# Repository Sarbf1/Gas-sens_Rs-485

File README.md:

# Gas-sens_Rs-485
a Compact, cheap gas sensor with RS-485 connectivity

## Concept:
24V supplied, Gas detector with half-duplex RS-485 interface. For industrial or home use and application ready product, containing a current or voltage output for reference measurment.
a sinlge LED used for showing cominucation or Error state. The small footprint makes it ready for most plastic enclosures.
the PCB can be hand-solderd with a bit of skill. 
Use cases can be in Garage systems (linked with the vents and gas alarm system), hobbyist workshop or any other room such as Office spaces and schools.

## Components

A STM32G031K8 is the logical unit. Is is cheap and readily available.
The very most components use standart fooprints. Thus, they are easily exchangeble in case of a shortage.
All parts are SMD, except for the Sensors, DCDC converter and Connectors.
All PCB components can be sourced by Mouser, except for the Gas Sensor.
For developement purposes (TAG v0.1) a gas sensor type MQ-X were used (MQ-7 and MQ-135)
TAG v0.2 makes use of the nemoto sensor, that uses low current and is more gas specific. 
The I2C conection gives a possibility, to further extend with more sensors, such as the Sensirion SHT4X.

## Programming
Hardware is developed in KiCad 7.0.

everything is programmed on STM Cube IDE. The Sensor and trim potentiometers are read-in using DMA.
The max and minimum values of the potentiometers can be set by the Modbus. the specific address are found in the excel-table "Modbus-memorymap" in the software folder.

## Simulation
Low pass filter for the PWM (from uC to OpAmp to voltag eand current output) has been simulated using LTSpice.

## next steps
- [X] PWM filter simulations
- [x] build and test prototype
- [x] Prgram IC for analog measurment and analog output
- [x] Find better sensor supplier and include it on second version PCB -> nemoto sensors
- [x] implement Modbus via RS-485
- [ ] create Bill of material
- [x] Make second physical prototype

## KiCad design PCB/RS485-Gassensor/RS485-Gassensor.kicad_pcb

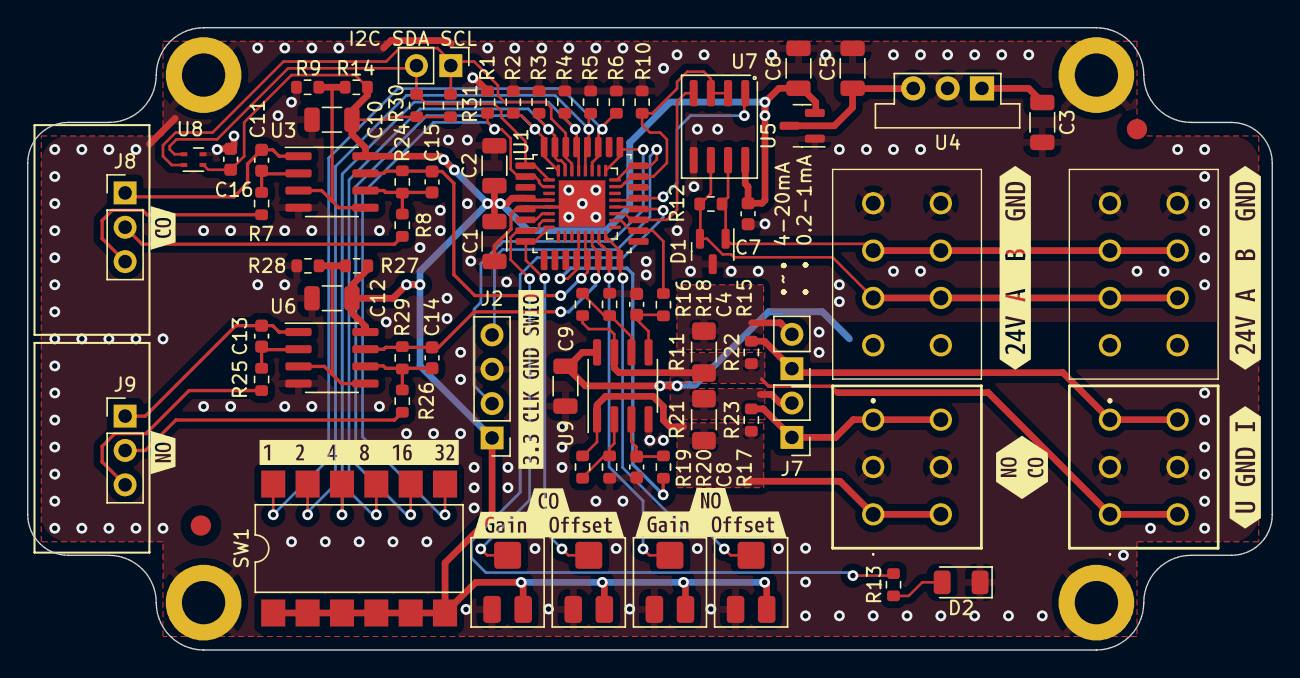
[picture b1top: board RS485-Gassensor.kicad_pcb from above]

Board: 2 copper layers, 92.0 x 46.0 mm, 91 parts (0 on the bottom side), 52 nets.

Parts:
C1: CAP4.7uF; C_1206_3216Metric
C2: CAP100nF; C_1206_3216Metric
C3: CAP10uF; C_1206_3216Metric
C4, C8: 470nF; C_0603_1608Metric
C5: CAP22uF; C_1206_3216Metric
C6, C9, C10, C12: CAP1uF; C_1206_3216Metric
C7, C16: CAP100nF; C_0603_1608Metric
C11, C13, C14, C15: CAP1uF; C_0603_1608Metric
D1: SM712_SOT23; SOT-23
D2: IR26-21C_L110_TR8; LED_1206_3216Metric
FID1, FID2: Fiducial; Fiducial_1.5mm_Mask3mm
H1, H2, H3, H4: MountingHole_Pad; MountingHole_3.2mm_M3_DIN965_Pad
J1, J3: Screw_Terminal_01x08; 1862068
J2: Screw_Terminal_01x04; PinHeader_1x04_P2.54mm_Vertical
J4, J5: Screw_Terminal_01x06; 1071000
J6, J7: Conn_01x02_Pin; PinHeader_1x02_P2.54mm_Vertical
J8, J9: Conn_01x03; PinHeader_1x03_P2.54mm_Vertical
J10: Conn_01x02; PinHeader_1x02_P2.54mm_Vertical
R1, R2, R3, R4, R5, R6, R7, R10, R24, R25, R29, R30, R31: R10K; R_0603_1608Metric
R8, R26: 10; R_0603_1608Metric
R9, R15, R17, R27, R28: 1k; R_0603_1608Metric
R11, R21: R470; R_1206_3216Metric_Pad1.30x1.75mm_HandSolder
R12: R220; R_0603_1608Metric
R13: R100; R_0603_1608Metric
R14, R16, R19: 2.2k; R_0603_1608Metric
R18, R20: R1K; R_0603_1608Metric
R22, R23: 10KR; R_0603_1608Metric
RV1, RV2, RV3, RV4: R_Poti_1K; Potentiometer_Bourns_3214J_Horizontal
SW1: SW_DIP_x06; SMDIP-12_W9.53mm
U1: STM32G031K8Tx; LQFP-32_7x7mm_P0.8mm
U2: STM32G031K8Ux; QFN-32-1EP_5x5mm_P0.5mm_EP3.45x3.45mm
U3, U6: MCP6002-xMS; SOIC-8_3.9x4.9mm_P1.27mm
U4: OKI-78SR-5_1.5-W36-C; Converter_DCDC_Murata_OKI-78SR_Vertical
U5: AP2127N-3.3; SOT-23
U7: LT1785xS8; SOIC-8_3.9x4.9mm_P1.27mm
U8: SHT4x; Sensirion_DFN-4_1.5x1.5mm_P0.8mm_SHT4x_NoCentralPad
U9: AD8676; SOIC-8_3.9x4.9mm_P1.27mm
kibuzzard-64E925B6: G***; kibuzzard-64E925B6
kibuzzard-64E958EB: G***; kibuzzard-64E958EB
kibuzzard-64E958FD: G***; kibuzzard-64E958FD
kibuzzard-64E92756: G***; kibuzzard-64E92756
kibuzzard-64ECCA5B: G***; kibuzzard-64ECCA5B
kibuzzard-64ECCA80: G***; kibuzzard-64ECCA80
kibuzzard-64ECCBAE: G***; kibuzzard-64ECCBAE
kibuzzard-651DD8EE: G***; kibuzzard-651DD8EE
kibuzzard-651DD908: G***; kibuzzard-651DD908
kibuzzard-650224BF: G***; kibuzzard-650224BF
kibuzzard-650224CC: G***; kibuzzard-650224CC
kibuzzard-650224F1: G***; kibuzzard-650224F1

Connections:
+3.3V: C1.1, C2.1, C6.1, C7.1, C10.1, C12.1, C16.2, J2.1, R14.2, R27.2, R30.2, R31.1, RV1.1, RV2.1, RV3.1, RV4.1, SW1.1, SW1.2, SW1.3, SW1.4, SW1.5, SW1.6, U1.4 (VDD), U2.4 (VDD), U3.8 (V+), U5.2 (VO), U6.8 (V+), U7.8 (VCC), U8.3 (VDD)
+5V: C5.1, U4.3 (OUT), U5.3 (VI)
+24V: C3.1, C9.1, J1.1, J1.2, J3.1, J3.2, U4.1 (IN), U9.8 (V+)
/Inputs and sensors/Counter_CO: C11.1, J8.1, U3.1
/Inputs and sensors/Counter_NO: C13.1, J9.1, U6.1
/Inputs and sensors/Reference_CO: J8.3, R7.1
/Inputs and sensors/Reference_NO: J9.3, R25.1
/Inputs and sensors/Working_CO: J8.2, R8.1
/Inputs and sensors/Working_NO: J9.2, R26.1
CO: C15.2, R24.2, U1.13 (PA6), U2.13 (PA6), U3.7
DIP0: R1.1, SW1.7, U1.2 (PC14), U2.2 (PC14)
DIP1: R2.1, SW1.8, U1.32 (PB8), U2.32 (PB8)
DIP2: R3.1, SW1.9, U1.31 (PB7), U2.31 (PB7)
DIP3: R4.1, SW1.10, U1.29 (PB5), U2.29 (PB5)
DIP4: R5.1, SW1.11, U1.28 (PB4), U2.28 (PB4)
DIP5: R6.1, SW1.12, U1.27 (PB3), U2.27 (PB3)
GND: C1.2, C2.2, C3.2, C4.2, C5.2, C6.2, C7.2, C8.2, C9.2, C10.2, C12.2, C16.1, D1.3 (common), D2.1 (K), H1.1, H2.1, H3.1, H4.1, J1.7, J1.8, J2.3, J3.7, J3.8, J4.3, J4.4, J5.3, J5.4, R1.2, R2.2, R3.2, R4.2, R5.2, R6.2, R9.1, R10.2, R18.2, R20.2, R28.1, RV1.3, RV2.3, RV3.3, RV4.3, U1.5 (VSS), U2.5 (VSS), U2.33 (VSS), U3.4 (V-), U4.2 (GND), U5.1 (GND), U6.4 (V-), U7.5 (GND), U8.4 (VSS), U9.4 (V-)
Gain_CO: RV1.2, U1.7 (PA0), U2.7 (PA0)
Gain_NO: RV3.2, U1.15 (PB0), U2.15 (PB0)
I2C_SCL: J10.1, R31.2, U1.30 (PB6), U2.30 (PB6), U8.2 (SCL)
I2C_SDA: J10.2, R30.1, U1.1 (PB9), U2.1 (PB9), U8.1 (SDA)
I_Out_CO: J5.5, J5.6, J6.1, R22.2
I_Out_NO: J4.5, J4.6, J7.1, R23.2
LED: R13.2, U1.20 (PC6), U2.20 (PC6)
NO2: C14.2, R29.2, U1.14 (PA7), U2.14 (PA7), U6.7
unnamed: D2.2 (A), R13.1
unnamed: J6.2, R11.2
unnamed: J7.2, R21.2
unnamed: R9.2, R14.1, U3.3 (+), U3.5 (+)
unnamed: C11.2, R7.2, U3.2 (-)
unnamed: C15.1, R8.2, R24.1, U3.6 (-)
unnamed: R27.1, R28.2, U6.3 (+), U6.5 (+)
unnamed: C13.2, R25.2, U6.2 (-)
unnamed: C14.1, R26.2, R29.1, U6.6 (-)
unnamed: C8.1, R17.2, U9.3 (+)
unnamed: R19.2, R20.1, U9.2 (-)
unnamed: C4.1, R15.2, U9.5 (+)
unnamed: R16.2, R18.1, U9.6 (-)
RS485-A: D1.2 (A2), J1.3, J1.4, J3.3, J3.4, R12.1, U7.6 (A)
RS485-B: D1.1 (A1), J1.5, J1.6, J3.5, J3.6, R12.2, U7.7 (B)
Read_!Enable: R10.1, U1.23 (PA12/PA10), U2.23 (PA12/PA10), U7.2 (~RE), U7.3 (DE)
SWCLK: J2.2, U1.25 (PA14), U2.25 (PA14)
SWDIO: J2.4, U1.24 (PA13), U2.24 (PA13)
T_NRST-Button: U1.6 (PF2), U2.6 (PF2)
UART_RX: U1.21 (PA10/NC), U2.21 (PA10/NC), U7.1 (RO)
UART_TX: U1.19 (PA9/NC), U2.19 (PA9/NC), U7.4 (DI)
U_Out_CO: J5.1, J5.2, R11.1, R16.1, R22.1, U9.7
U_Out_NO: J4.1, J4.2, R19.1, R21.1, R23.1, U9.1
analog_PWM_CO: R15.1, U1.18 (PA8), U2.18 (PA8)
analog_PWM_NO: R17.1, U1.12 (PA5), U2.12 (PA5)
offset_CO: RV2.2, U1.8 (PA1), U2.8 (PA1)
offset_NO: RV4.2, U1.16 (PB1), U2.16 (PB1)

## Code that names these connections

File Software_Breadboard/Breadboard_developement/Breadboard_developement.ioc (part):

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Mcu.Name=STM32G031K(4-6-8)Tx
Mcu.Package=LQFP32
Mcu.UserName=STM32G031K8Tx
PA0.GPIOParameters=GPIO_Label
PA0.GPIO_Label=ADC1_IN0_GAIN_CO
PA0.Mode=IN0
PA0.Signal=ADC1_IN0
PA1.GPIOParameters=GPIO_Label
PA1.GPIO_Label=ADC1_IN1_OFFSET_CO
PA1.Mode=IN1
PA1.Signal=ADC1_IN1
PA10.Mode=Asynchronous
PA10.Signal=USART1_RX
PA12\ [PA10].Mode=Hardware Flow Control (RS485)
PA12\ [PA10].Signal=USART1_DE
PA13.GPIOParameters=GPIO_Label
PA13.GPIO_Label=T_JTMS
PA13.Mode=Serial_Wire
PA13.Signal=SYS_SWDIO
PA14-BOOT0.GPIOParameters=GPIO_Label
PA14-BOOT0.GPIO_Label=T_JTCK
PA14-BOOT0.Mode=Serial_Wire
PA14-BOOT0.Signal=SYS_SWCLK
PA2.GPIOParameters=GPIO_PuPd,GPIO_Label
PA2.GPIO_Label=T_VCP_TX
PA2.GPIO_PuPd=GPIO_PULLUP
PA2.Mode=Asynchronous
PA2.Signal=USART2_TX
PA3.GPIOParameters=GPIO_PuPd,GPIO_Label
PA3.GPIO_Label=T_VCP_RX
PA3.GPIO_PuPd=GPIO_PULLUP
PA3.Mode=Asynchronous
PA3.Signal=USART2_RX
PA5.GPIOParameters=GPIO_Label
PA5.GPIO_Label=TIM2_CH1_PWM_NO
PA5.Signal=S_TIM2_CH1_ETR
PA6.GPIOParameters=GPIO_Label
PA6.GPIO_Label=ADC1_IN6_CO
PA6.Mode=IN6
PA6.Signal=ADC1_IN6
PA7.GPIOParameters=GPIO_Label
PA7.GPIO_Label=ADC1_IN7_NO
PA7.Mode=IN7
PA7.Signal=ADC1_IN7
PA8.GPIOParameters=GPIO_Label
PA8.GPIO_Label=TIM1_CH1_PWM_CO
PA8.Signal=S_TIM1_CH1
PA9.Mode=Asynchronous
PA9.Signal=USART1_TX
PB0.GPIOParameters=GPIO_Label
PB0.GPIO_Label=ADC1_IN8_GAIN_NO
PB0.Mode=IN8
PB0.Signal=ADC1_IN8
PB1.GPIOParameters=GPIO_Label
PB1.GPIO_Label=ADC1_IN9_OFFSET_NO
PB1.Mode=IN9
PB1.Signal=ADC1_IN9
PB3.GPIOParameters=GPIO_Label
PB3.GPIO_Label=GPIO_IN_DIP5
PB3.Signal=GPIO_Input
PB4.GPIOParameters=GPIO_Label
PB4.GPIO_Label=GPIO_IN_DIP4
PB4.Signal=GPIO_Input
PB5.GPIOParameters=GPIO_Label
PB5.GPIO_Label=GPIO_IN_DIP3
PB5.Signal=GPIO_Input
PB6.GPIOParameters=GPIO_Label
PB6.GPIO_Label=GPIO_IN_DIP2
PB6.Signal=GPIO_Input
PB7.GPIOParameters=GPIO_Label
PB7.GPIO_Label=GPIO_IN_DIP1
PB7.Signal=GPIO_Input
PB8.GPIOParameters=GPIO_Label
PB8.GPIO_Label=GPIO_IN_DIP0
PB8.Signal=GPIO_Input
PC14-OSC32_IN\ (PC14).Mode=LSE-External-Oscillator
PC14-OSC32_IN\ (PC14).Signal=RCC_OSC32_IN
PC15-OSC32_OUT\ (PC15).Mode=LSE-External-Oscillator
PC15-OSC32_OUT\ (PC15).Signal=RCC_OSC32_OUT
PC6.GPIOParameters=GPIO_Label
PC6.GPIO_Label=LD3 [Green]
PC6.Signal=GPIO_Output
PF2\ -\ NRST.GPIOParameters=GPIO_Label
PF2\ -\ NRST.GPIO_Label=T_NRST
PF2\ -\ NRST.Signal=GPXTI2
RCC.HSE_VALUE=8000000
RCC.SYSCLKFreq_VALUE=16000000
board=NUCLEO-G031K8
boardIOC=true

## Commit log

2023-07-04 Create LICENSE.md
    aded apache 2.0 License
2023-07-04 Create .gitignore
    added gitignore for C, windows, Kicad
2023-07-04 added PCB
    added Kicad PCB
2023-07-04 Update README.md
    added current status and todo
2023-07-06 clean up, minor extension
    cleaned up /reorganized scematic,
    added optional termination resistor for RS-485
2023-08-20 restarted Project.
    new PCB, improved component chioce
    strarted program with STM32 IDE
2023-08-27 new PCB
    new PCB, working DMA
2023-10-03 imoproved filter
    one dual channel Op amp, corrections from first produced prototype
2023-10-03 Update README.md Tickboxes
2023-10-25 added Modbus / RS485
2024-01-18 made For NAP505 and NAP550
2024-02-08 code and hardware imrovement V2
    added I2C, and modbus functionailties
2024-02-08 update screenshots
